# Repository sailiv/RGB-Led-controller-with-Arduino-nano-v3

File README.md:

# RGB Led controller with Arduino nano v3
#
* Controler have 7 programs
* S1 and S2 change program
* S3 reset MCU
* R4 (POT) change the brightness

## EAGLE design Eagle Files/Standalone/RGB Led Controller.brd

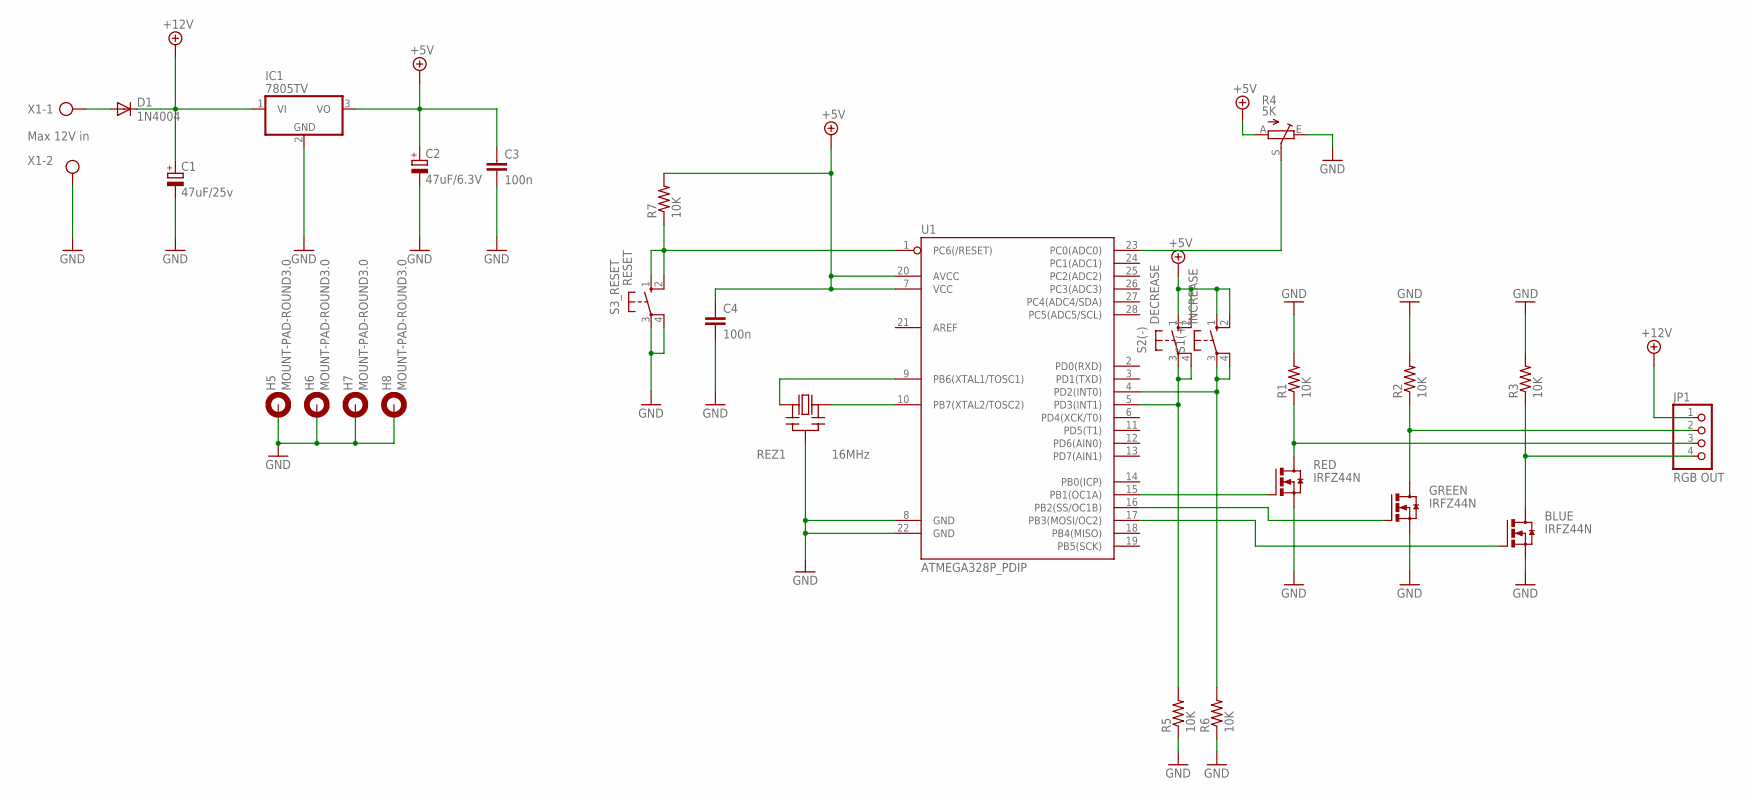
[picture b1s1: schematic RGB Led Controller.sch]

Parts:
BLUE: IRFZ44N; TO220V
C1: 47uF/25v; E5-10,5
C2: 47uF/6.3V; E5-10,5
C3, C4: 100n; CAP-PTH-SMALLEZ
D1: 1N4004; DO41-10
GREEN: IRFZ44N; TO220V
H5, H6, H7, H8: MOUNT-PAD-ROUND3.0; 3,0-PAD
IC1: 7805TV; TO220V
JP1: RGB OUT; 1X04
R1, R2, R3, R5, R6, R7: 10K; 0309/12
R4: 5K; CIP20C-6MM
RED: IRFZ44N; TO220V
REZ1: 16MHz; CERM_OSC
S1(+): INCREASE; B3F-10XX
S2(-): DECREASE; B3F-10XX
S3_RESET: RESET; B3F-10XX
U1: ATMEGA328P_PDIP; DIL28-3
X1: Max 12V in; AK300/2

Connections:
+5V: C2.+, C3.1, C4.1, IC1.3 (VO), R4.A, R7.2, S1(+).1 (S), S1(+).2 (S1), S2(-).1 (S), S2(-).2 (S1), U1.7 (VCC), U1.20 (AVCC)
+12V: C1.+, D1.C, IC1.1 (VI), JP1.1
GND: BLUE.3 (S), C1.-, C2.-, C3.2, C4.2, GREEN.3 (S), H5.B3,0, H6.B3,0, H7.B3,0, H8.B3,0, IC1.2 (GND), R1.2, R2.2, R3.2, R4.E, R5.1, R6.1, RED.3 (S), REZ1.P$2 (GND), S3_RESET.3, S3_RESET.4 (P1), U1.8 (GND), U1.22 (GND), X1.2
unnamed: REZ1.P$1 (IN), U1.9 (PB6(XTAL1/TOSC1))
unnamed: REZ1.P$3 (OUT), U1.10 (PB7(XTAL2/TOSC2))
unnamed: RED.1 (G), U1.15 (PB1(OC1A))
unnamed: GREEN.1 (G), U1.16 (PB2(SS/OC1B))
unnamed: BLUE.1 (G), U1.17 (PB3(MOSI/OC2))
unnamed: BLUE.2 (D), JP1.4, R3.1
unnamed: GREEN.2 (D), JP1.2, R2.1
unnamed: JP1.3, R1.1, RED.2 (D)
unnamed: R4.S, U1.23 (PC0(ADC0))
unnamed: R7.1, S3_RESET.1 (S), S3_RESET.2 (S1), U1.1 (PC6(/RESET))
unnamed: D1.A, X1.1
unnamed: R5.2, S2(-).3, S2(-).4 (P1), U1.5 (PD3(INT1))
unnamed: R6.2, S1(+).3, S1(+).4 (P1), U1.4 (PD2(INT0))

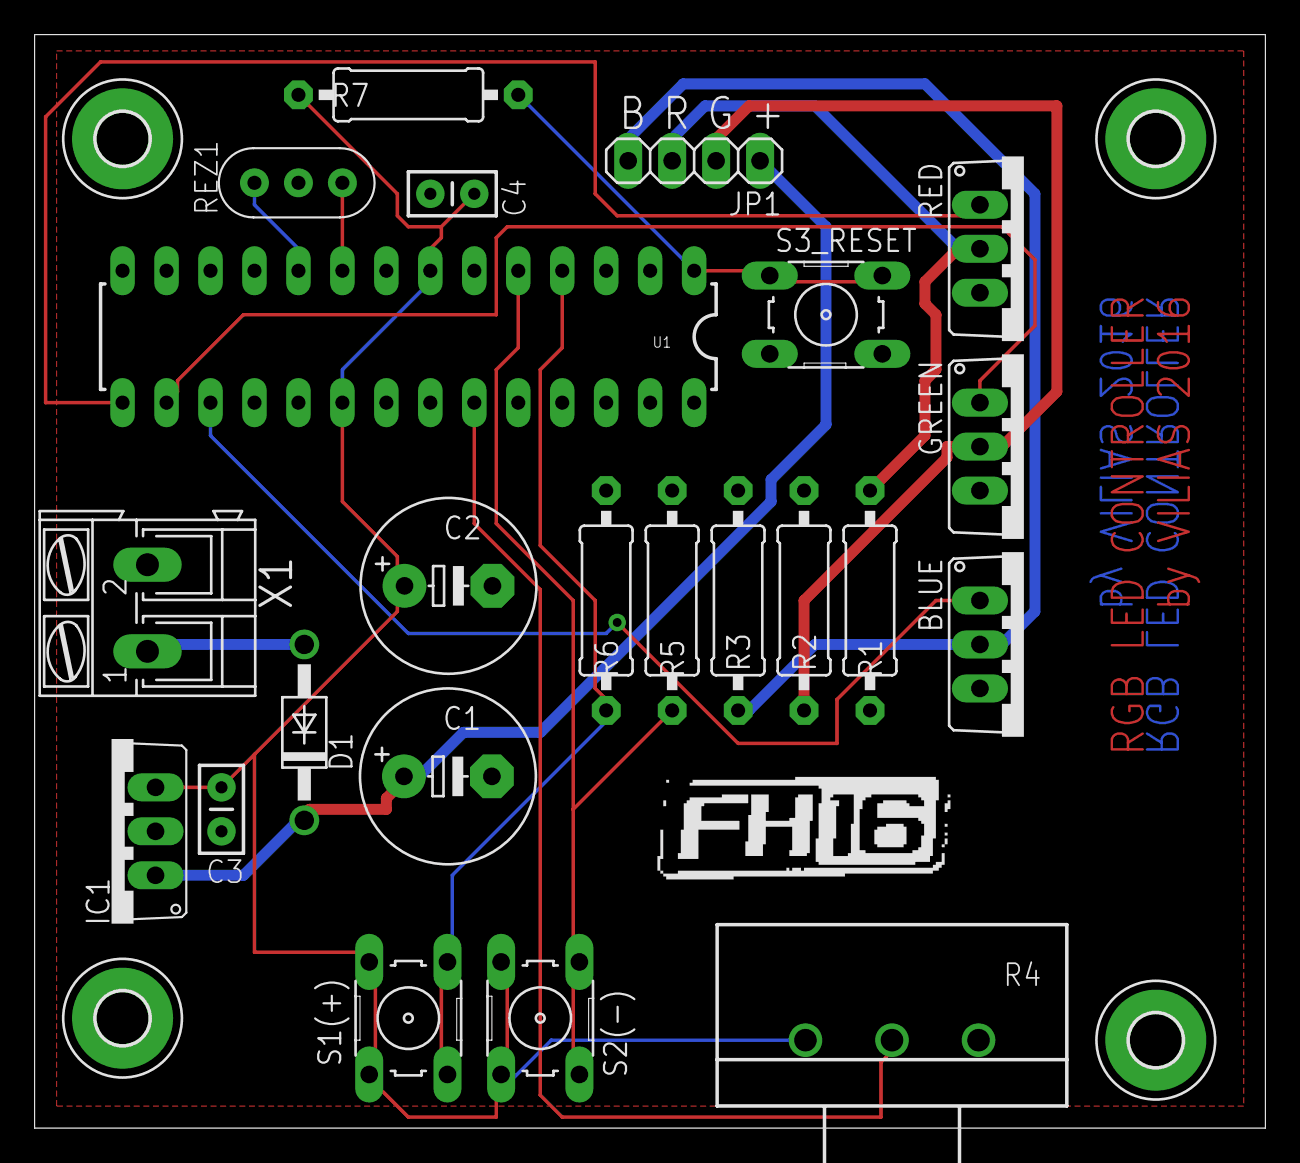
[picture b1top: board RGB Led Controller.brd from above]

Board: 2 copper layers, 71.1 x 63.2 mm, 27 parts (0 on the bottom side), 16 nets.

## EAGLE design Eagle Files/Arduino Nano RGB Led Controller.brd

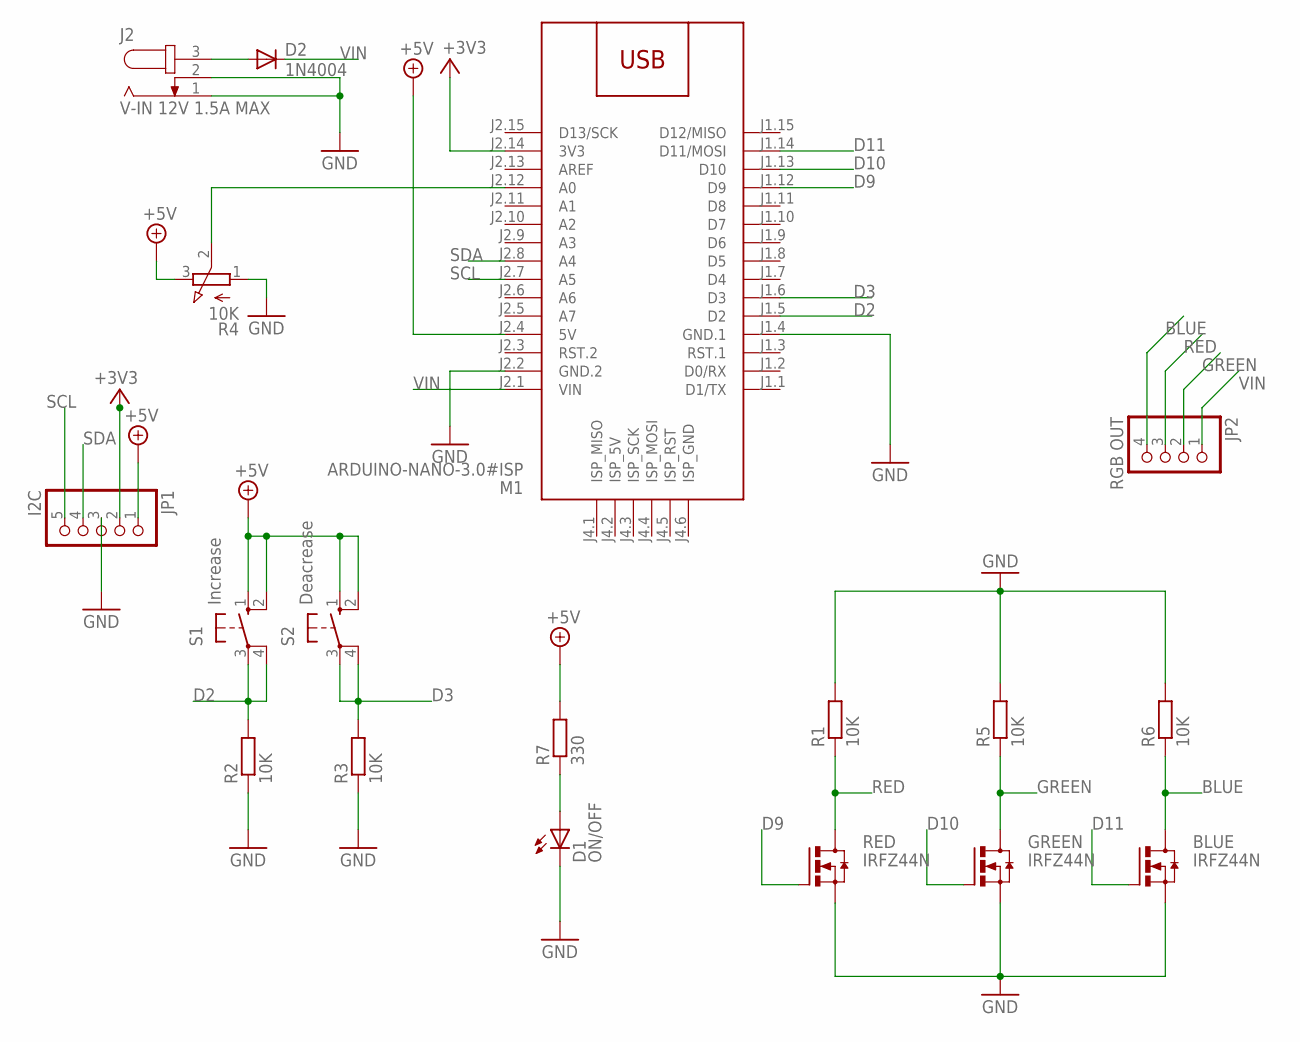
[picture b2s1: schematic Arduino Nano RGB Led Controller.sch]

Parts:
BLUE: IRFZ44N; TO220V
D1: ON/OFF; CHIPLED_1206
D2: 1N4004; DO41-10
GREEN: IRFZ44N; TO220V
J2: V-IN 12V 1.5A MAX; SPC4078
JP1: I2C; 1_05X2MM
JP2: RGB OUT; 1X04
M1: ARDUINO-NANO-3.0#ISP
R1, R2, R3, R5, R6: 10K; M1206
R4: 10K; 3RP/1610N
R7: 330; M1206
RED: IRFZ44N; TO220V
S1: Increase; B3F-10XX
S2: Deacrease; B3F-10XX

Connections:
+3V3: JP1.2, M1.J2.14 (3V3)
+5V: JP1.1, M1.J2.4 (5V), R4.3 (E), R7.2, S1.1 (S), S1.2 (S1), S2.1 (S), S2.2 (S1)
BLUE: BLUE.2 (D), JP2.4, R6.1
D2: M1.J1.5 (D2), R2.2, S1.3, S1.4 (P1)
D3: M1.J1.6 (D3), R3.2, S2.3, S2.4 (P1)
D9: M1.J1.12 (D9), RED.1 (G)
D10: GREEN.1 (G), M1.J1.13 (D10)
D11: BLUE.1 (G), M1.J1.14 (D11/MOSI)
GND: BLUE.3 (S), D1.C, GREEN.3 (S), J2.1, J2.2, JP1.3, M1.J1.4 (GND.1), M1.J2.2 (GND.2), R1.2, R2.1, R3.1, R4.1 (A), R5.2, R6.2, RED.3 (S)
GREEN: GREEN.2 (D), JP2.2, R5.1
unnamed: M1.J2.12 (A0), R4.2 (S)
unnamed: D1.A, R7.1
unnamed: D2.A, J2.3
RED: JP2.3, R1.1, RED.2 (D)
SCL: JP1.5, M1.J2.7 (A5)
SDA: JP1.4, M1.J2.8 (A4)
VIN: D2.C, JP2.1, M1.J2.1 (VIN)

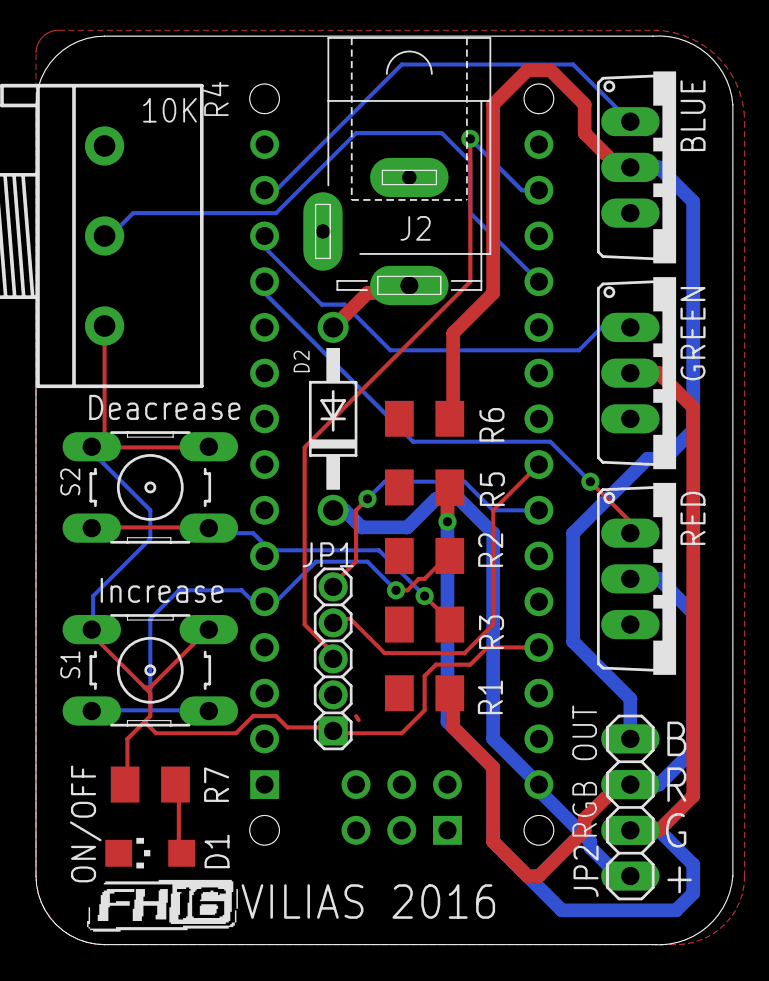
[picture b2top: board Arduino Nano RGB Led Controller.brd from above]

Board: 2 copper layers, 38.7 x 50.5 mm, 18 parts (1 on the bottom side), 17 nets.

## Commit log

2016-07-25 :circus_tent: Added .gitattributes & .gitignore files
2016-07-25 last commit
2016-07-26 Revert "last commit"
    This reverts commit 8cb80f48c1e68596feebbafeaeea08a93ed3c69f.
2016-07-28 Update PCB
2016-07-28 Added standalone files
2016-07-28 Logo added at pcb file
    My Logo added at pcb file
2016-08-17 update stand alone

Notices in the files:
parts and their libraries:
diy-modules: Released under the Creative Commons Attribution 4.0 International License: http://creativecommons.org/licenses/by/4.0
SparkFun-DigitalIC: Licensing: Creative Commons ShareAlike 4.0 International - https://creativecommons.org/licenses/by-sa/4.0
